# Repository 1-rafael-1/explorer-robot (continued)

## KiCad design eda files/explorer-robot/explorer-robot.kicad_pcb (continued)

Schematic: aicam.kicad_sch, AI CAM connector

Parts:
C54, C55: 1u; C_0603_1608Metric; MPN CL10A105KB8NNNC; LCSC C15849
C60: 10u; C_0805_2012Metric; MPN CL21A106KAYNNNE; LCSC C15850
J8: AI.CAM; JST_PH_B4B-PH-K_1x04_P2.00mm_Vertical
R18, R19, R20: 100; R_0603_1608Metric; MPN 0603WAF1000T5E; LCSC C22775
U9: TPS22917DBV; SOT-23-6; MPN TPS22917DBVR; LCSC C2681320

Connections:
+5V: C55.2, U9.1 (VIN); also elsewhere on the board
/AI CAM/AICAM_PWR: U9.3 (ON); also elsewhere on the board
/AI CAM/AICAM_RX: R18.1; also elsewhere on the board
/AI CAM/AICAM_TX: R19.1; also elsewhere on the board
GND: C54.1, C55.1, C60.2, J8.2, U9.2 (GND); also elsewhere on the board
unnamed: C54.2, C60.1, J8.1, R20.1, U9.6 (VOUT)
unnamed: J8.3, R18.2
unnamed: J8.4, R19.2
unnamed 112: U9.4 (CT); also elsewhere on the board
unnamed: R20.2, U9.5 (QOD)

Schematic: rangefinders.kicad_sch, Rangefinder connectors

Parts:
C63, C65: 10u; C_0805_2012Metric; MPN CL21A106KAYNNNE; LCSC C15850
C64, C66: 100n; C_0603_1608Metric; MPN CC0603KRX7R9BB104; LCSC C14663
J13: RF.FRONT; JST_PH_B6B-PH-K_1x06_P2.00mm_Vertical
J14: RF.REAR; JST_PH_B6B-PH-K_1x06_P2.00mm_Vertical
R37, R38, R41, R42: 33; R_0603_1608Metric; MPN 0603WAF330JT5E; LCSC C23140
R39, R40, R43, R44: 4k7; R_0603_1608Metric; MPN 0603WAF4701T5E; LCSC C23162

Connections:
+3.3V: C63.1, C64.1, C65.1, C66.1, J13.1, J14.1, R39.1, R40.2, R43.1, R44.2; also elsewhere on the board
/Rangefinders/I2C0_SCL: R37.1; also elsewhere on the board
/Rangefinders/I2C0_SDA: R38.1; also elsewhere on the board
/Rangefinders/I2C1_SCL: R41.1; also elsewhere on the board
/Rangefinders/I2C1_SDA: R42.1; also elsewhere on the board
/Rangefinders/RF_FRONT_INT: J13.5; also elsewhere on the board
/Rangefinders/RF_FRONT_XSHUT: J13.6; also elsewhere on the board
/Rangefinders/RF_REAR_INT: J14.5; also elsewhere on the board
/Rangefinders/RF_REAR_XSHUT: J14.6; also elsewhere on the board
GND: C63.2, C64.2, C65.2, C66.2, J13.2, J14.2; also elsewhere on the board
unnamed: J13.3, R37.2, R39.2
unnamed: J13.4, R38.2, R40.1
unnamed: J14.3, R41.2, R43.2
unnamed: J14.4, R42.2, R44.1

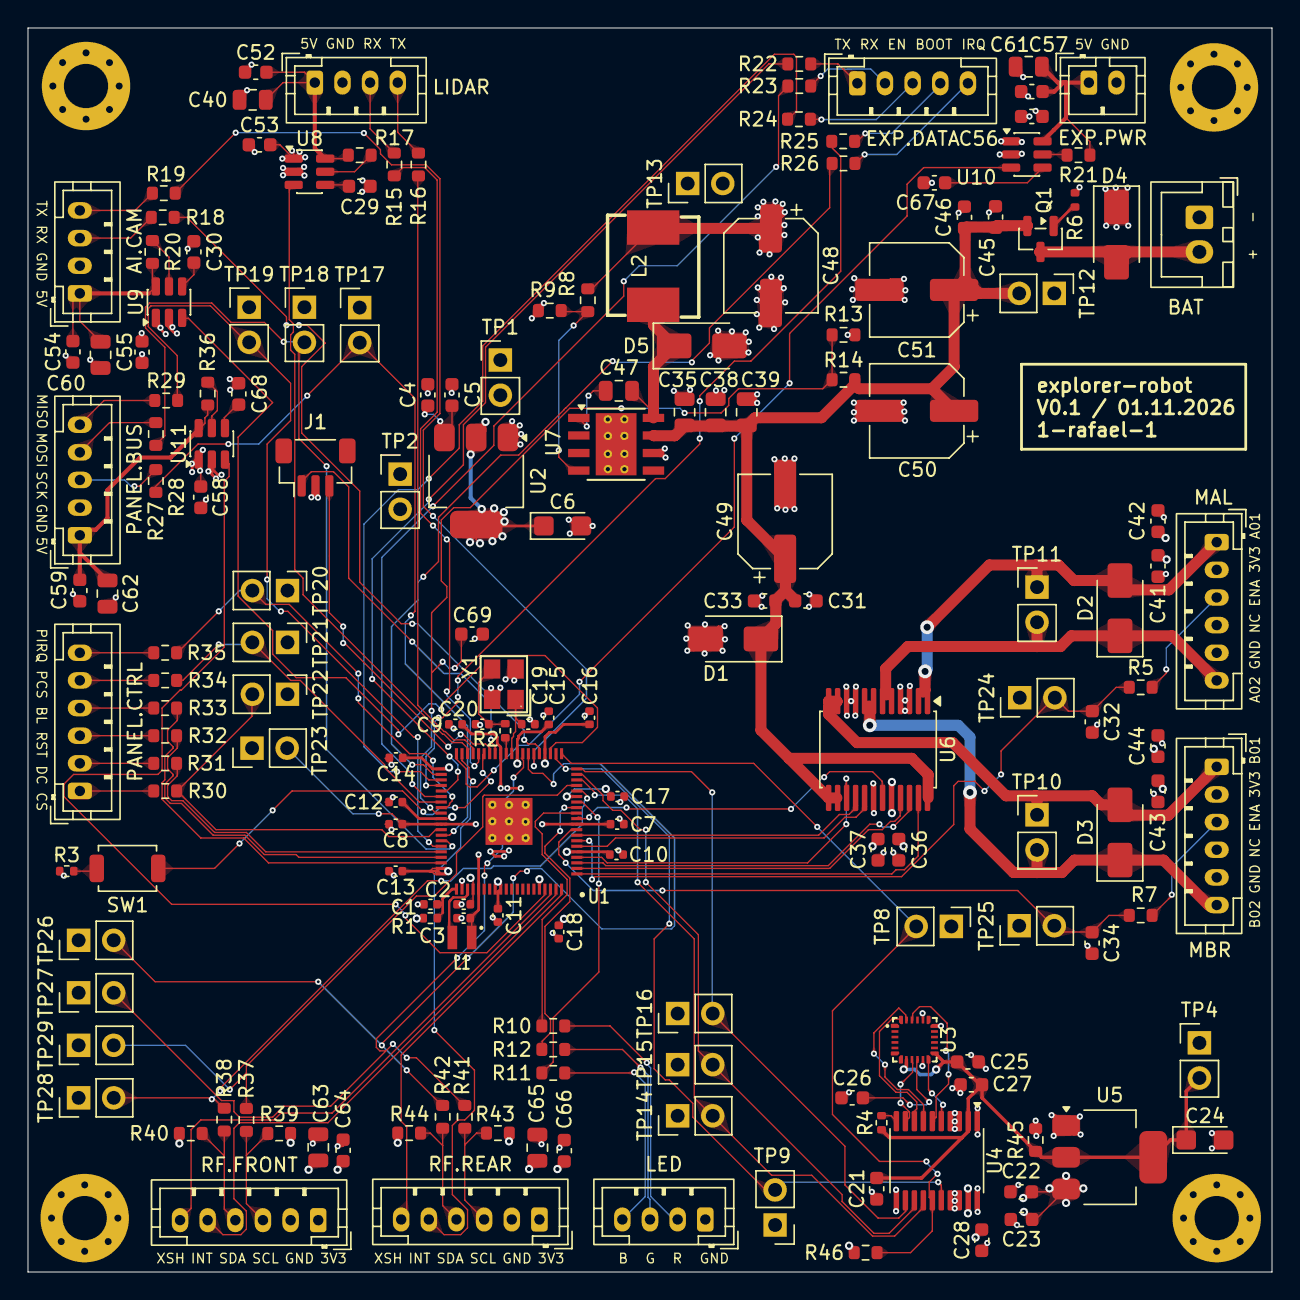
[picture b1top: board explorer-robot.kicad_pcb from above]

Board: 4 copper layers, 90.0 x 90.0 mm, 178 parts (0 on the bottom side), 118 nets.

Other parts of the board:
C30, C68: 1n; C_0603_1608Metric
C69: 100n; C_0603_1608Metric
H1, H2, H3, H4: MountingHole_Pad; MountingHole_3.2mm_M3_Pad_Via
R46: 2K2; R_0603_1608Metric

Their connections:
+3.3V: R46.2; also elsewhere on the board
+5V: C30.2, C68.2; also elsewhere on the board
/ICM-20948/ICM-20948_CS: R46.1; also elsewhere on the board
/Power and Battery/BATT_ADC: C69.2; also elsewhere on the board
GND: C69.1, H1.1 (1_1), H2.1 (1_1), H3.1 (1_1), H4.1 (1_1); also elsewhere on the board
unnamed 112: C30.1; also elsewhere on the board
unnamed 116: C68.1; also elsewhere on the board

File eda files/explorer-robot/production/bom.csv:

Designator,Footprint,Quantity,Value,LCSC Part #
"C1, C2, C3",0402,3,4.7u,C23733
"C10, C11, C12, C13, C14, C15, C16, C17, C18, C7, C8, C9",0402,12,100n,
"C19, C20",0402,2,15p,
"C21, C25, C26, C27, C28, C31, C37, C41, C43, C45, C64, C66",0603,12,100n,C14663
"C22, C23, C4, C5",0603,4,10u,C19702
"C24, C6",CP_EIA-3216-18_Kemet-A,2,22u,C11366
"C29, C30, C67, C68",0603,4,1n,
"C32, C34",0603,2,2n2,C57112
"C33, C36, C42, C44, C46, C52, C53, C54, C55, C56, C57, C58, C59",0603,13,1u,C15849
"C35, C38, C39, C40, C60, C61, C62, C63, C65",0805,9,10u,C15850
C47,0805,1,10n,C1710
"C48, C49, C50, C51",CP_Elec_6.3x7.7,4,220u,C42371908
C69,0603,1,100n,
"D1, D2, D3, D4",D_SMA,4,D_TVS,C20602531
D5,D_SMA,1,3A 40V,C8678
J1,JST_SH_BM03B-SRSS-TB_1x03-1MP_P1.00mm_Vertical,1,DBG,C7430452
L1,abracon_aota-b201610s3r3-101-t,1,3.3u,C42411119
L2,IND-SMD_L7.1-W6.6_SLO0618H,1,15u,
Q1,SOT-23,1,Q_PMOS_GSD,C15127
R1,0402,1,33,C25105
"R10, R11",0603,2,220,C22962
R12,0603,1,330,C23138
"R13, R8",0603,2,10K,C25804
R14,0603,1,33K,C4184
"R15, R16, R17, R18, R19, R20, R21, R22, R23, R30, R31, R32, R33, R34, R36",0603,15,100,C22775
R2,0402,1,1K,
"R24, R25, R26, R35",0603,4,1k,C21190
"R27, R28, R29, R37, R38, R41, R42",0603,7,33,C23140
R3,0402,1,1K,C11702
"R39, R40, R43, R44",0603,4,4k7,C23162
"R4, R6",0402,2,100K,C25741
R45,0603,1,150,
R46,0603,1,2K2,
"R5, R7",0603,2,2.2K,C4190
R9,0603,1,3K3,C22978
SW1,SW_SPST_TS-1088-xR020,1,SW_Push,C720477
U1,rpi_rp2350b_vias,1,RP2354B,C39843328
"U10, U11, U8, U9",SOT-23-6,4,TPS22917DBV,C2681320
U2,SOT-223-3_TabPin2,1,AMS1117-3.3,C6186
U3,QFN-24_L3.0-W3.0-P0.40-BL-EP,1,ICM-20948,
U4,TSSOP-20_4.4x6.5mm_P0.65mm,1,TXB0108PW,C53406
U5,SOT-223-3_TabPin2,1,AMS1117-1.8,C347220
U6,SSOP-24_5.3x8.2mm_P0.65mm,1,TB6612FNG,C141517
U7,TI_SO-PowerPAD-8_ThermalVias,1,TPS5430DDA,C9864
Y1,CRYSTAL-SMD_4P-L3.2-W2.5-BL,1,ABM8-272-T3,C20625731

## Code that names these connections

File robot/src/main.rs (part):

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
/// Build the Link Port session and spawn its task on core0.
///
/// The session retains UART1, the GPIO 36/37 pads, `EXP_PWR`/`EXP_EN`/`EXP_BOOT`,
/// `EXP_IRQ` and the hardware TRNG. No UART is constructed at boot: the task
/// builds one per powered period, after it has asserted the branch and waited
/// for the switch rise (ADR-0023, ADR-0032).
///
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    info!("explorer-robot v3 booting...");

    // Why did the previous run end? The POWMAN flags are sticky across resets, so
    // this distinguishes a brownout/glitch from a debugger or RUN-pin reset.
    #[cfg(feature = "telemetry_logs")]
    {
        let reset = embassy_rp::pac::POWMAN.chip_reset().read();
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
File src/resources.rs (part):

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        /// Display backlight (GPIO 47).
        blk: PIN_47,
        /// Touch chip select (GPIO 38).
        touch_cs: PIN_38,
        /// Touch pen-down interrupt (GPIO 39, active-low with a pull-up).
        penirq: PIN_39,
        /// TPS22917 high-side load-switch enable (`PANEL_PWR`, active-high, GPIO 0).
        power_enable: PIN_0,
    }

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    /// Resources for the 7-pin expansion connector (not yet implemented).
    ///
    /// The 5 V branch is switched by a TPS22917 high-side load switch enabled by
    /// `EXP_PWR` on GPIO 32. The connector uses UART1 on GPIO 36/37, with reset/
    /// enable on GPIO 34, boot-mode on GPIO 35, and interrupt/status on GPIO 33.
    /// Its logic is 3.3 V; the 5 V pin is power, not a logic reference. Quiesce
    /// UART1 and hold `en`/`boot` low before switching the branch off (ADR-0023).
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        tx_dma: DMA_CH4,
        /// UART1 RX DMA channel.
        rx_dma: DMA_CH5,
        /// TPS22917 high-side load-switch enable (`EXP_PWR`, active-high, GPIO 32).
        power_enable: PIN_32,
        /// Expansion interrupt/status line (GPIO 33).
        irq: PIN_33,
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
